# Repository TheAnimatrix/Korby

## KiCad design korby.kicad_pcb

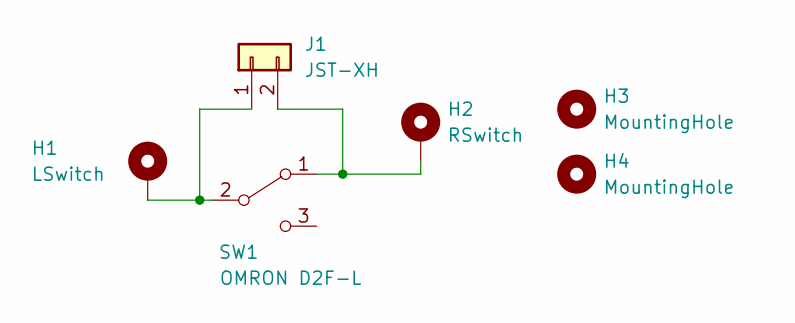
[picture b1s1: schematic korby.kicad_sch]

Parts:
H1: LSwitch; MountingHole_3.2mm_M3_DIN965_Pad
H2: RSwitch; MountingHole_3.2mm_M3_DIN965_Pad
H3, H4: MountingHole; MountingHole_3.2mm_M3_DIN965_Pad
J1: JST-XH; JST_XH_B2B-XH-AM_1x02_P2.50mm_Vertical
SW1: OMRON D2F-L; SW_D2F-FL

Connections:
unnamed: H1.1, J1.1, SW1.2 (B)
unnamed: H2.1, J1.2, SW1.1 (A)

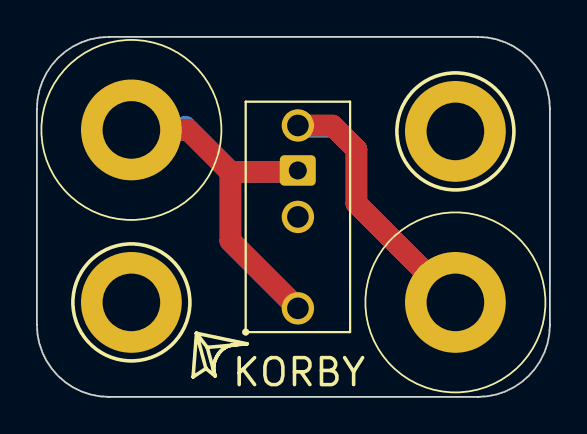
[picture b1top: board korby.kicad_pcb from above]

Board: 2 copper layers, 28.5 x 20.0 mm, 6 parts (1 on the bottom side), 2 nets.

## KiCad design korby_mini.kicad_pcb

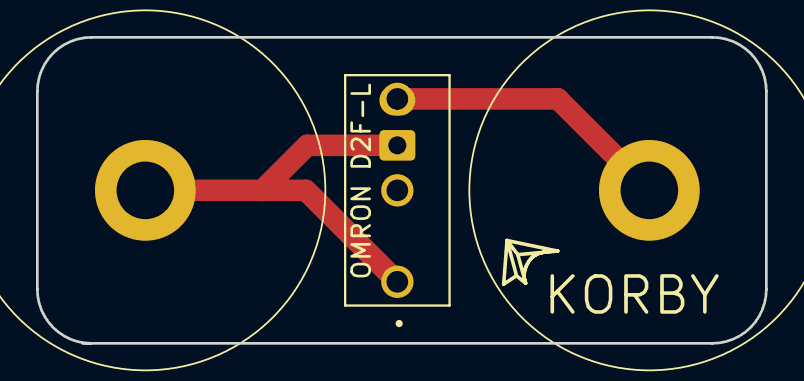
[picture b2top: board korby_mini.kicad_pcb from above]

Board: 2 copper layers, 40.5 x 17.0 mm, 4 parts (1 on the bottom side), 2 nets.

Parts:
H1: LSwitch; MountingHole_3.2mm_M3_DIN965_Pad
H2: RSwitch; MountingHole_3.2mm_M3_DIN965_Pad
JST: JST-XH; JST_XH_B2B-XH-A_1x02_P2.50mm_Vertical
SW1: OMRON D2F-L; SW_D2F-FL

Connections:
unnamed: H1.1, JST.1, SW1.2 (B)
unnamed: H2.1, JST.2, SW1.1 (A)

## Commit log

2024-09-05 genesis
